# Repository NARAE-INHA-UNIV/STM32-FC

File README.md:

**본 문서는 STM32 firmware만을 다루고 있습니다.**

> [[STM32-FC-docs]](https://github.com/NARAE-INHA-UNIV/STM32-FC-docs) How to use, Specification <br>
> [[STM32-FC-hw]](https://github.com/NARAE-INHA-UNIV/STM32-FC-hw) KiCAD, Schematic, PCB Artwork <br>
> [[MiniLink_cli]](https://github.com/NARAE-INHA-UNIV/MiniLink_cli) Data analysis like msg, log, param <br>

-----

# STM32 FC

인하대학교 모형항공기 동아리 나래에서 2024년 동계 UAV 활동으로 진행한 프로젝트임. <br>
회로와 펌웨어를 개발하되, 기성 pixhawk 모듈과 호환성을 가지기 위해 pixhawk 6C mini의 인터페이스와 흡사하게 제작하는 것을 목표로함. <br>

- 활동명 : [UAV] FC 제작 활동
- 일시 : 2024 동계 방학 - 진행중
- 팀명 :  항공전자 (구 FC)
- 팀장 : 정영우(2025), 이현제(2024)

## 폴더 구조

`Plane` 폴더가 STM32Cube IDE 프로젝트이다. 주로 수정할 코드는 `Core` 디렉토리 내에 위치한다.

`Plane` -> `Core` -> `Src/Inc`

- Src : Source code (.c)
- Inc : header (.h)
  - {Module Name}.h
  - {Module Name}_module.h
  - {Module Name}_common.h
  - {Module Name}_type.h

{Module Name} 앞의 접두사의 의미 :
- `FC` : 보드 내부 HW 관리 (UART, RC, Servo etc.)
- `AP` : 고수준의 제어기나 자율 비행 (Failsafe, RTH etc.)
- `SEN` : 외부 센서

헤더 파일 중 `driver.h`는 외부 모듈에서 접근할 떄 사용한다. <br>
예를 들어 `main.c`가 `RadioContol` 모듈에 접근할 때 `FC_RC/driver.h`에 접근해야 한다. `RadioContol.h`는 해당 모듈 내부에서 사용하는 코드로 외부에서 직접 접근하지 않도록 한다.

```bash
├─AP_Failsafe       # Failsafe 관련 코드
├─FC_AHRS           # IMU 센서, 기압 센서
├─FC_Basic          # Buzzer나 LED 등
├─FC_RC             # 라디오 조종기 (스펙트럼, PPM, ELRS)
├─FC_Servo          # 서보 모터, ESC
├─FC_Serial         # Serial 기능
│  └─MiniLink       # 외부 장치와 통신하는 프로토콜
│      └─Param      # 파라미터 관리
└─test              # 테스트 중인 코드
```

## 기여 (개발)

1. 프로젝트 fork
2. fork된 개인 레파지토리 clone
3. 코드 작성
4. 개인 레파지토리에 커밋 & 푸시
5. Pull-request

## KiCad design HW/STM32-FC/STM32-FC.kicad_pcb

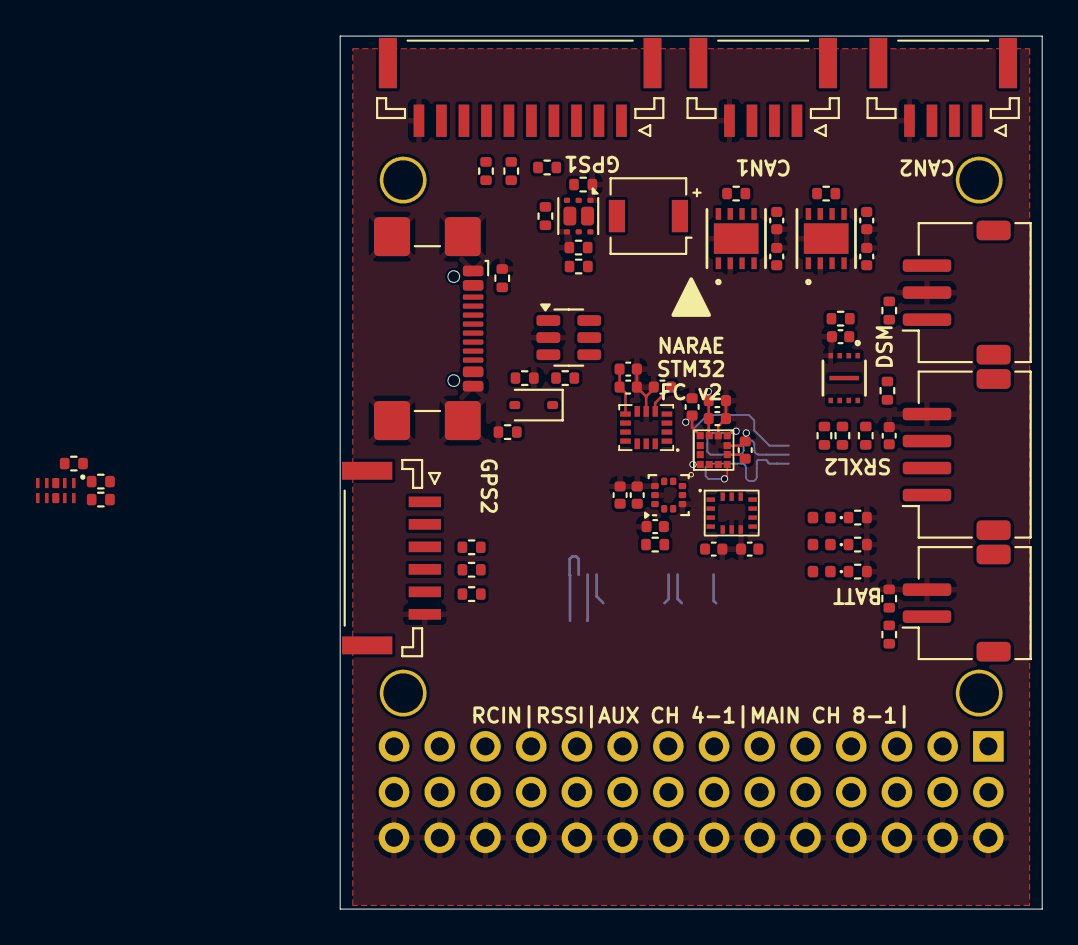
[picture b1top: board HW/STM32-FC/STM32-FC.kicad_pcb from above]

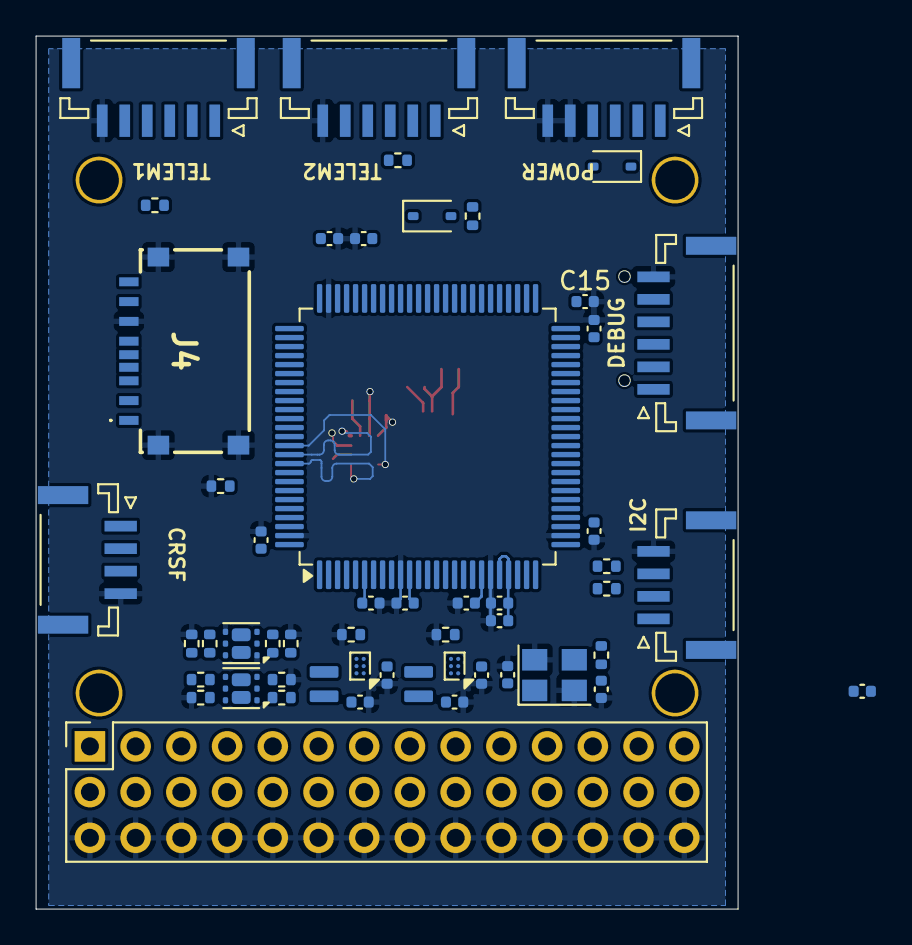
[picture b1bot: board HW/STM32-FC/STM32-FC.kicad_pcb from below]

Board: 4 copper layers, 39.0 x 48.5 mm, 129 parts (53 on the bottom side), 120 nets.

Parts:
BZ1: FUET-4020
C1, C4: 10pF; C_0402_1005Metric
C2, C14, C16, C27: 4.7uF; C_0402_1005Metric
C3, C5, C8, C9, C10, C11, C13, C15, C20, C21, C22, C23, C24, C29, C30, C32, C33, C34, C35, C36, C37: 100nF; C_0402_1005Metric
C6, C7, C25: 2.2uF; C_0402_1005Metric
C12: 1uF; C_0402_1005Metric
C17, C19, C28: 10uF; C_0402_1005Metric
C26: 10nF; C_0402_1005Metric
C31: 220nF; C_0402_1005Metric
D1, D5, D6: B5819W; D_SOD-323
D2: Red; LED_0402_1005Metric
D3: Yellow; LED_0402_1005Metric
D4: Green; LED_0402_1005Metric
H1, H2, H3, H4: MountingHole; MountingHole_2.2mm_M2
J1, J3, J11, J12, J13: GH 1.25mm 6P; JST_GH_SM06B-GHS-TB_06x1.25mm_Angled
J2: USB_C_USB2.0_14P; USB_C_Receptacle_GCT_USB4110
J4: TF-06A; TF06A
J5: JST ZH 1.5mm 2P; JST_ZH_S2B-ZR-SM4A-TF_1x02-1MP_P1.50mm_Horizontal
J6: PWM_Conn_3x14
J7: ZH 1.5mm 4P; JST_ZH_S4B-ZR-SM4A-TF_1x04-1MP_P1.50mm_Horizontal
J8, J14, J15, J16: GH 1.25mm 4P; JST_GH_SM04B-GHS-TB_04x1.25mm_Angled
J9: ZH 1.5mm 3P; JST_ZH_S3B-ZR-SM4A-TF_1x03-1MP_P1.50mm_Horizontal
J10: GH 1.25mm 10P; JST_GH_SM10B-GHS-TB_10x1.25mm_Angled
L1, L3: 2.2u; VLS201610ET-2R2M
Q1, Q2: PMDPB30XN; Nexperia_SOT1118
Q3: PMDPB55XP; Nexperia_SOT1118
R1, R2, R5, R11, R12, R23, R24, R25, R26, R27, R28, R31, R32, R34, R36, R37, R38, R39, R40, R41, R42, R43, R44, R45, R46, R47: 10k; R_0402_1005Metric
R3, R4, R6, R7, R8, R9, R10, R33, R48, R49: 120; R_0402_1005Metric
R13, R14: 5k1; R_0402_1005Metric
R15, R16, R17, R18, R30, R35: 1k; R_0402_1005Metric
R19: 1k5; R_0402_1005Metric
R20, R22: 267k; R_0402_1005Metric
R29: 15k; R_0402_1005Metric
U1: STM32F407VETx; LQFP-100_14x14mm_P0.5mm
U2: USBLC6-2SC6; SOT-23-6
U3, U5: TPS62840; Texas_DSBGA-6_0.855x1.255mm_Layout2x3_P0.4mm_LevelC
U6: W25X40CLUXIG; USON_LUXIG TR_WIN-L
U7: BMI323; BMI323_L
U8: ICM-42688-P; IIM42352_L
U9: LIS2MDLTR
U10: LPS22HH; ST_HLGA-10_2x2mm_P0.5mm_LayoutBorder3x2y
U11: TMUX1104
U12, U13: ATA6561-GBQW; VDFN8_3X3_MCH-L
Y1: 16MHz; Crystal_SMD_Abracon_ABM8G-4Pin_3.2x2.5mm

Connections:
+3.3V: C2.1, C3.1, C8.1, C9.1, C10.1, C11.1, C12.1, C13.1, C15.1, C17.1, C19.1, C20.1, C21.1, C22.1, C23.1, C24.2, C25.1, C26.1, C27.2, C28.1, C29.1, C30.1, C32.2, C33.2, C36.2, C37.2, J1.1, J4.4 (VDD), J9.1, J10.8, L1.2, L3.2, R19.1, R23.1, R24.1, R25.1, R26.1, R28.1, R35.1, R36.1, R38.1, R39.1, R40.1, R41.1, R42.1, R43.1, R44.1, R45.1, R46.1, R47.1, U1.6 (VBAT), U1.11 (VDD), U1.19 (VDD), U1.21 (VREF+), U1.22 (VDDA), U1.28 (VDD), U1.50 (VDD), U1.75 (VDD), U1.100 (VDD), U3.A2 (VOS), U5.A2 (VOS), U6.3 (~WP), U6.7 (~HOLD), U6.8 (VCC), U7.5 (VDDIO), U7.8 (VDD), U8.5 (VDDIO), U8.8 (VDD), U9.9 (VDD), U9.10 (VDD_IO), U10.1 (Vdd_IO), U10.10 (VDD), U11.5 (EN), U11.6 (VDD), U12.5 (VIO), U13.5 (VIO)
+5V: BZ1.1 (-), C14.1, C16.1, C34.2, C35.2, D1.1 (K), D5.1 (K), D6.1 (K), J6.17 (5V_RCIN), J6.18 (5V_RSSI), J7.3, J8.3, J10.1, J11.1, J12.1, J13.1, J14.1, J15.1, J16.1, Q3.1 (S), Q3.4 (S), R15.1, R16.1, U3.B1 (VIN), U3.C1 (EN), U5.B1 (VIN), U12.3 (VCC), U13.3 (VCC)
+5V_PWM1: J6.15 (5V_A), Q3.6 (D), Q3.7 (D), R17.1
+5V_PWM2: J6.16 (5V_B), Q3.3 (D), Q3.8 (D), R18.1
+BATT: J5.1, R29.1
/BARO_INT: U1.38 (PE7), U10.7 (INT_DRDY)
/BARO_NSS: R28.2, U1.5 (PE6), U10.6 (~CS)
/BOOT0: J1.5, R2.1, U1.94 (BOOT0)
/Buzzer: R4.1, U1.61 (PD14)
/CAN1_RX: U1.81 (PD0), U12.4 (RXD)
/CAN1_STBY: U1.33 (PC4), U12.8 (STBY)
/CAN1_TX: U1.82 (PD1), U12.1 (TXD)
/CAN2_RX: U1.51 (PB12), U13.4 (RXD)
/CAN2_STBY: U1.34 (PC5), U13.8 (STBY)
/CAN2_TX: U1.92 (PB6), U13.1 (TXD)
/Communication/CAN1_N: J15.3, R48.2, U12.6 (CANL)
/Communication/CAN1_P: J15.2, R48.1, U12.7 (CANH)
/Communication/CAN2_N: J16.3, R49.2, U13.6 (CANL)
/Communication/CAN2_P: J16.2, R49.1, U13.7 (CANH)
/FLASH_NSS: U1.7 (PC13), U6.1 (~CS)
/GPS1_BUZZER: J10.9, U1.65 (PC8)
/GPS1_SW: J10.6, U1.60 (PD13)
/GPS1_SW_LED: J10.7, U1.57 (PD10)
/GYRO1_INT: U1.39 (PE8), U8.4 (INT1/INT)
/GYRO1_NSS: U1.4 (PE5), U8.12 (AP_CS)
/GYRO2_INT: U1.8 (PC14), U7.4 (INT1)
/GYRO2_NSS: U1.2 (PE3), U7.12 (CSB)
/I2C1_SCL: J14.2, R47.2, U1.95 (PB8)
/I2C1_SDA: J14.3, R46.2, U1.96 (PB9)
/I2C2_SCL: J11.4, R42.2, U1.47 (PB10)
/I2C2_SDA: J11.5, R40.2, U1.48 (PB11)
/I2C3_SCL: J10.4, R39.2, U1.67 (PA8)
/I2C3_SDA: J10.5, R38.2, U1.66 (PC9)
/LED_GREEN: D4.2 (A), U1.1 (PE2)
/LED_RED: D2.2 (A), U1.97 (PE0)
/LED_YELLOW: D3.2 (A), U1.98 (PE1)
/MAG_NSS: U1.3 (PE4), U9.3 (CS)
/MSD_DETECT: R27.1, U1.9 (PC15)
/MSD_NSS: J4.2 (CS), R26.2, U1.88 (PD7)
/NRST: C5.1, J1.4, U1.14 (NRST)
/OSC_IN: C1.2, U1.12 (PH0), Y1.1
/OSC_OUT: R3.2, U1.13 (PH1)
/PM_CURRENT: J3.3, U1.17 (PC2)
/PM_VOLTAGE: J3.4, U1.18 (PC3)
/PWR_SEL0: R9.1, U1.46 (PE15)
/PWR_SEL1: R10.1, U1.77 (PA15)
/RC_INPUT/RCIN: J6.14 (RCIN), U11.8 (D)
/RC_INPUT/SBUS: R33.1, U11.9 (S2)
/RC_PPM: R37.1, U1.45 (PE14), U11.2 (S1)
/RC_RX: J8.2, J9.3, Q1.3 (D), Q1.8 (D), R35.2, R36.2, U1.69 (PA10), U11.4 (S3)
/RC_SEL0: R31.1, U1.41 (PE10), U11.1 (A0)
/RC_SEL1: R32.1, U1.40 (PE9), U11.10 (A1)
/RC_TX: J7.1, J8.1, U1.68 (PA9), U11.7 (S4)
/RSSI_IN: J6.13 (RSSI), U1.16 (PC1)
/SPI1_MISO: U1.31 (PA6), U8.1 (AP_SDO/AP_AD0), U10.5 (SA0)
/SPI1_MOSI: U1.32 (PA7), U8.14 (AP_SDA/AP_SDIO/AP_SDI), U10.4 (SDA)
/SPI1_SCK: U1.30 (PA5), U8.13 (AP_SCL/AP_SCLK), U10.2 (SCL)
/SPI2_MISO: J4.7 (DO), R23.2, U1.53 (PB14), U6.2 (DO(IO1))
/SPI2_MOSI: J4.3 (DI), R25.2, U1.54 (PB15), U6.5 (DI(IO0))
/SPI2_SCK: J4.5 (SCLK), R24.2, U1.52 (PB13), U6.6 (SCK)
/SPI3_MISO: U1.90 (PB4), U7.1 (SDO), U9.7 (INT/DRDY/SDO)
/SPI3_MOSI: U1.91 (PB5), U7.14 (SDX), U9.4 (SDA/SDI/SDO)
/SPI3_SCK: U1.89 (PB3), U7.13 (SCX), U9.1 (SCL/SPC)
/SWCLK: J1.3, U1.76 (PA14)
/SWDIO: J1.2, U1.72 (PA13)
/SW_PWR_IMU: U1.43 (PE12), U5.C1 (EN)
/TIM1_CH2: J6.11 (CH11), U1.42 (PE11)
/TIM1_CH3: J6.12 (CH12), U1.44 (PE13)
/TIM3_CH1: J6.2 (CH2), U1.63 (PC6)
/TIM3_CH2: J6.3 (CH3), U1.64 (PC7)
/TIM3_CH3: J6.9 (CH9), U1.35 (PB0)
/TIM3_CH4: J6.10 (CH10), U1.36 (PB1)
/TIM4_CH2: J6.1 (CH1), U1.93 (PB7)
/TIM4_CH4: J6.4 (CH4), U1.62 (PD15)
/TIM5_CH1: J6.5 (CH5), U1.23 (PA0)
/TIM5_CH2: J6.6 (CH6), U1.24 (PA1)
/TIM5_CH3: J6.7 (CH7), U1.25 (PA2)
/TIM5_CH4: J6.8 (CH8), U1.26 (PA3)
/UART2_CTS: J12.4, U1.84 (PD3)
/UART2_RTS: J12.5, U1.85 (PD4)
/UART2_RX: J12.3, R44.2, U1.87 (PD6)
/UART2_TX: J12.2, U1.86 (PD5)
/UART3_CTS: J13.4, U1.58 (PD11)
/UART3_RTS: J13.5, U1.59 (PD12)
/UART3_RX: J13.3, R45.2, U1.56 (PD9)
/UART3_TX: J13.2, U1.55 (PD8)
/UART4_RX: J10.3, R41.2, U1.79 (PC11)
/UART4_TX: J10.2, U1.78 (PC10)
/UART5_RX: J11.3, R43.2, U1.83 (PD2)
/UART5_TX: J11.2, U1.80 (PC12)
/USB & POWER/USB_CONN_D+: J2.A6 (D+), J2.B6 (D+), U2.3 (I/O2)
/USB & POWER/USB_CONN_D-: J2.A7 (D-), J2.B7 (D-), U2.1 (I/O1)
/USB_D+: R19.2, U1.71 (PA12), U2.4 (I/O2)
/USB_D-: U1.70 (PA11), U2.6 (I/O1)
/VCAP1: C6.2, U1.49 (VCAP_1)
/VCAP2: C7.1, U1.73 (VCAP_2)
/V_BATT: R29.2, R30.1, U1.15 (PC0)
GND: C1.1, C2.2, C3.2, C4.2, C5.2, C6.1, C7.2, C8.2, C9.2, C10.2, C11.2, C12.2, C13.2, C14.2, C15.2, C16.2, C17.2, C19.2, C20.2, C21.2, C22.2, C23.2, C24.1, C25.2, C26.2, C27.1, C28.2, C29.2, C30.2, C31.2, C32.1, C33.1, C34.1, C35.1, C36.1, C37.1, J1.6, J2.A1 (GND), J2.A12 (GND), J2.B1 (GND), J2.B12 (GND), J2.S1 (SHIELD), J3.5, J3.6, J4.6 (VSS), J4.MP1, J4.MP2, J4.MP3, J4.MP4, J5.2, J6.19 (GND), J7.4, J8.4, J9.2, J10.10, J11.6, J12.6, J13.6, J14.4, J15.4, J16.4, Q1.1 (S), Q1.4 (S), Q2.1 (S), Q2.4 (S), R1.2, R2.2, R5.2, R6.2, R7.2, R8.2, R11.2, R12.2, R13.2, R14.2, R17.2, R18.2, R20.1, R22.1, R30.2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
unnamed: BZ1.2 (+), D1.2 (A), Q1.6 (D), Q1.7 (D)
unnamed: C4.1, R3.1, Y1.3
unnamed: D2.1 (K), R6.1
unnamed: D3.1 (K), R7.1
unnamed: D4.1 (K), R8.1
unnamed: D6.2 (A), J3.1, J3.2
unnamed: J2.A5 (CC1), R13.1
unnamed: J2.B5 (CC2), R14.1
unnamed: J4.G1 (SWICTH), R27.2
unnamed: Q1.2 (G), R4.2, R5.1
unnamed: Q1.5 (G), R33.2, R34.1
unnamed: Q2.2 (G), R9.2, R11.1
unnamed: Q2.5 (G), R10.2, R12.1
unnamed: Q2.6 (D), Q2.7 (D), Q3.2 (G), R15.2
unnamed: Q2.3 (D), Q2.8 (D), Q3.5 (G), R16.2
unnamed: R1.1, U1.37 (PB2)
unnamed: L1.1, U3.B2 (SW)
unnamed: R20.2, U3.C2 (VSET)
unnamed: L3.1, U5.B2 (SW)
unnamed: R22.2, U5.C2 (VSET)
unnamed: C31.1, U9.5 (C1)
VBUS: D5.2 (A), J2.A4 (VBUS), J2.A9 (VBUS), J2.B4 (VBUS), J2.B9 (VBUS), U2.5 (VBUS)

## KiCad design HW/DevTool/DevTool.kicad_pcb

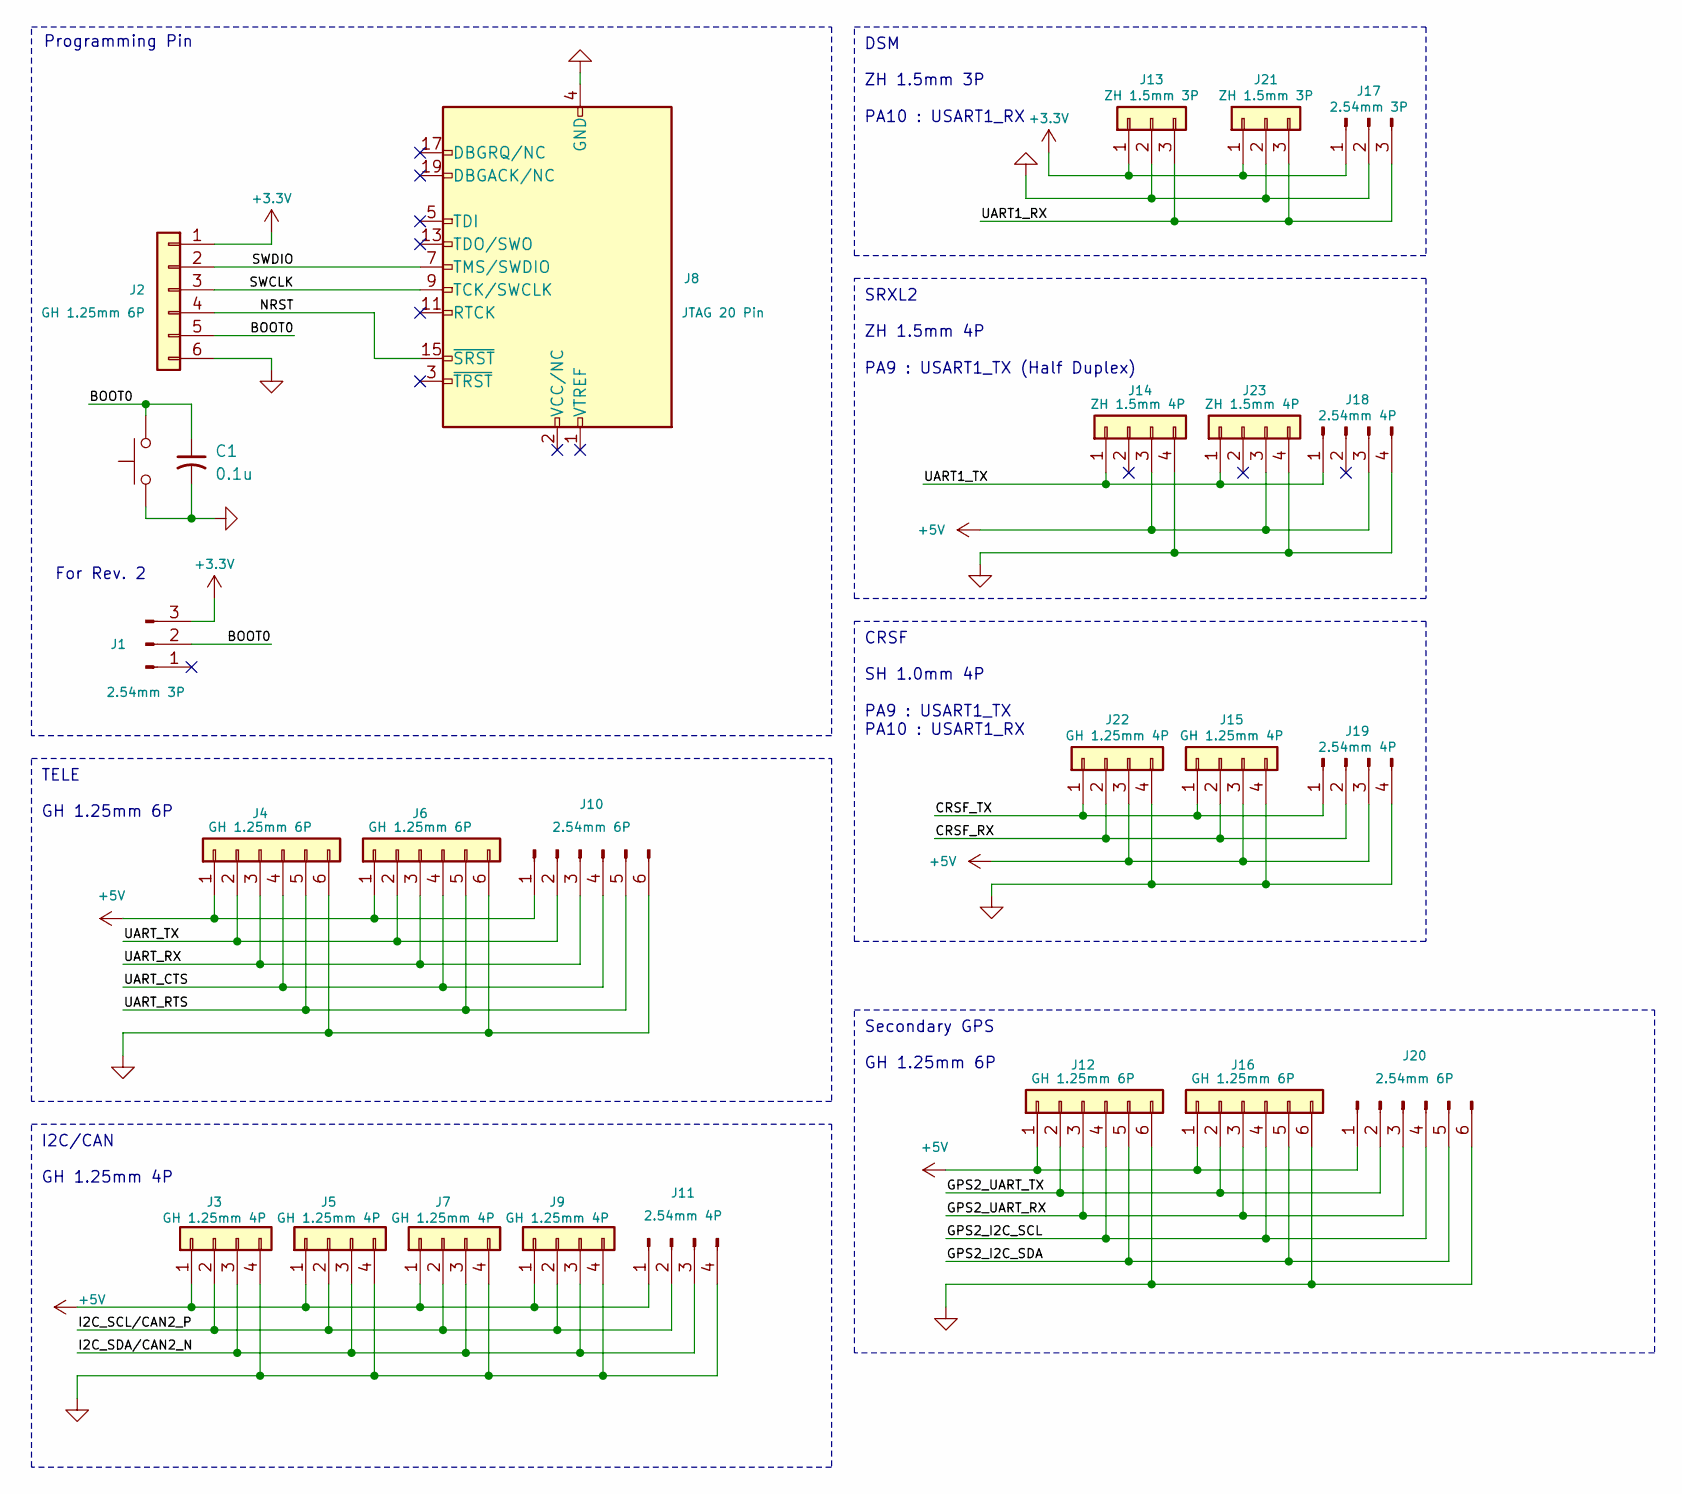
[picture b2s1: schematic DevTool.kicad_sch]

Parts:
C1: 0.1u; C_0603_1608Metric
J1, J17: 2.54mm 3P; PinHeader_1x03_P2.54mm_Vertical
J2, J4, J6, J12, J16: GH 1.25mm 6P; JST_GH_BM06B-GHS-TBT_06; LCSC C133065
J3, J5, J7, J9, J15, J22: GH 1.25mm 4P; JST_GH_BM04B-GHS-TBT_04; LCSC C189895
J8: JTAG 20 Pin; IDC-Header_2x10_P2.54mm_Vertical
J10, J20: 2.54mm 6P; PinHeader_1x06_P2.54mm_Vertical
J11, J18, J19: 2.54mm 4P; PinHeader_1x04_P2.54mm_Vertical
J13, J21: ZH 1.5mm 3P; JST_ZH_S3B-ZR-SM4A-TF_1x03-1MP_P1.50mm_Horizontal; LCSC C72591
J14, J23: ZH 1.5mm 4P; JST_ZH_S4B-ZR-SM4A-TF_1x04-1MP_P1.50mm_Horizontal; LCSC C485354
SW1: SW_Push; SW_SPST_PTS645

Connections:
+3.3V: J1.3, J2.1, J13.1, J17.1, J21.1
+5V: J3.1, J4.1, J5.1, J6.1, J7.1, J9.1, J10.1, J11.1, J12.1, J14.3, J15.3, J16.1, J18.3, J19.3, J20.1, J22.3, J23.3
/BOOT0: C1.1, J1.2, J2.5, SW1.2
/CRSF_RX: J15.2, J19.2, J22.2
/CRSF_TX: J15.1, J19.1, J22.1
/GPS2_I2C_SCL: J12.4, J16.4, J20.4
/GPS2_I2C_SDA: J12.5, J16.5, J20.5
/GPS2_UART_RX: J12.3, J16.3, J20.3
/GPS2_UART_TX: J12.2, J16.2, J20.2
/I2C_SCL/CAN2_P: J3.2, J5.2, J7.2, J9.2, J11.2
/I2C_SDA/CAN2_N: J3.3, J5.3, J7.3, J9.3, J11.3
/NRST: J2.4, J8.15 (~SRST)
/SWCLK: J2.3, J8.9 (TCK/SWCLK)
/SWDIO: J2.2, J8.7 (TMS/SWDIO)
/UART1_RX: J13.3, J17.3, J21.3
/UART1_TX: J14.1, J18.1, J23.1
/UART_CTS: J4.4, J6.4, J10.4
/UART_RTS: J4.5, J6.5, J10.5
/UART_RX: J4.3, J6.3, J10.3
/UART_TX: J4.2, J6.2, J10.2
GND: C1.2, J2.6, J3.4, J4.6, J5.4, J6.6, J7.4, J8.4 (GND), J8.6 (GND), J8.8 (GND), J8.10 (GND), J8.12 (GND), J8.14 (GND), J8.16 (GND), J8.18 (GND), J8.20 (GND), J9.4, J10.6, J11.4, J12.6, J13.2, J14.4, J15.4, J16.6, J17.2, J18.4, J19.4, J20.6, J21.2, J22.4, J23.4, SW1.1

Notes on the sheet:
SRXL2
CRSF
DSM
SH 1.0mm 4P PA9 : USART1_TX PA10 : USART1_RX
For Rev. 2
GH 1.25mm 6P
Programming Pin
TELE
GH 1.25mm 4P
ZH 1.5mm 3P PA10 : USART1_RX
I2C/CAN
Secondary GPS
ZH 1.5mm 4P PA9 : USART1_TX (Half Duplex)

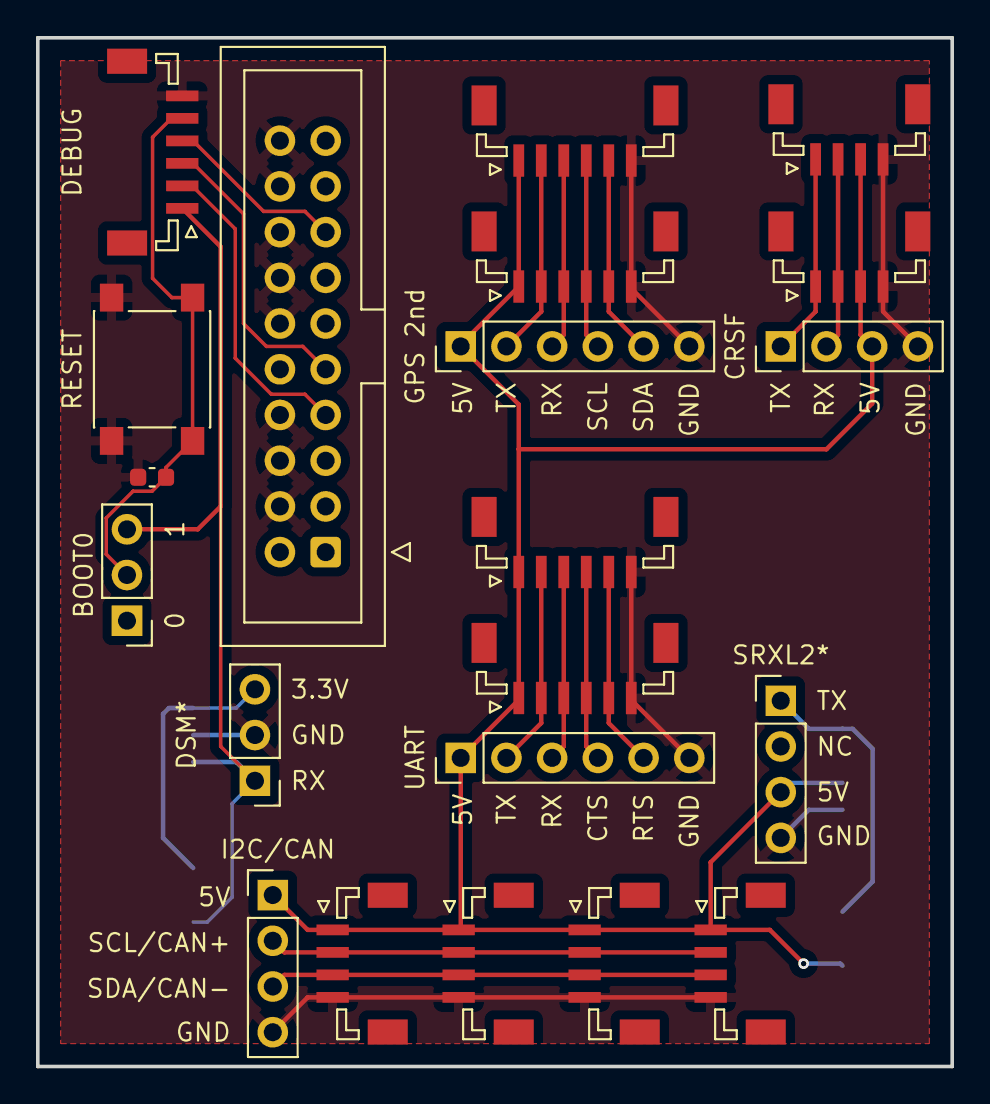
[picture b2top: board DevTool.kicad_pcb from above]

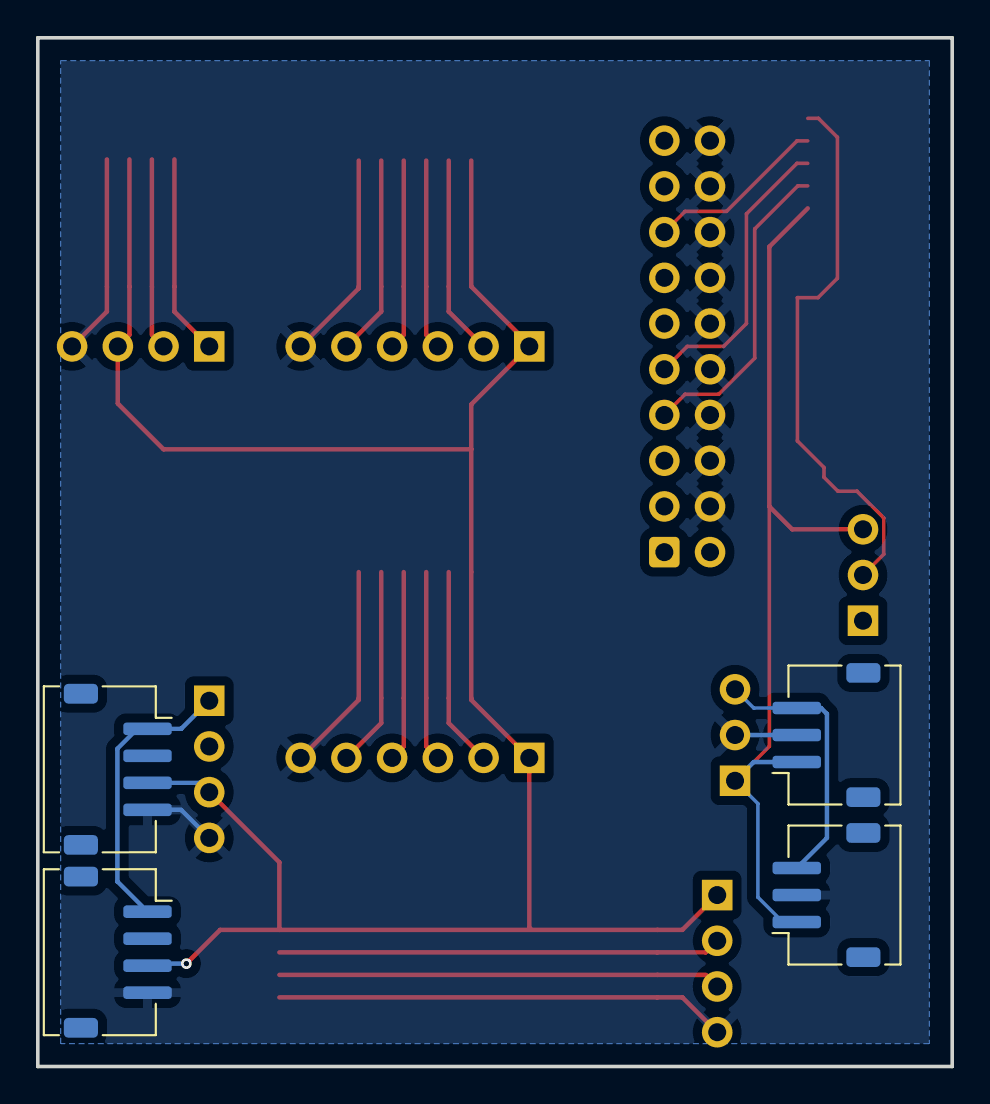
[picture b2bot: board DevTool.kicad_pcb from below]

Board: 2 copper layers, 50.8 x 57.2 mm, 25 parts (4 on the bottom side), 21 nets.

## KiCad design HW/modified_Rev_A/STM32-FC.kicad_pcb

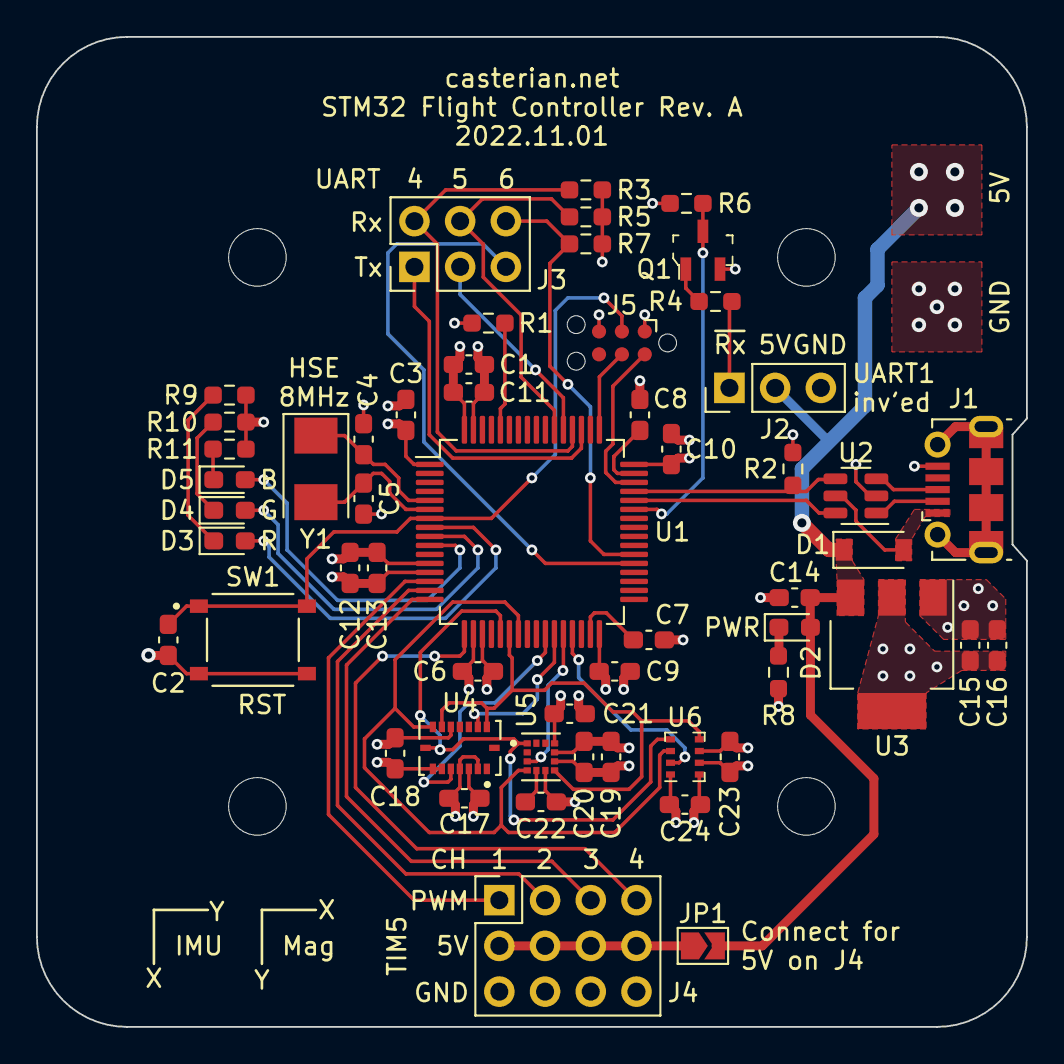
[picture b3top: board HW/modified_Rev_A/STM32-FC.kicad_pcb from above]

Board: 4 copper layers, 55.0 x 55.0 mm, 59 parts (0 on the bottom side), 45 nets.

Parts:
C1, C14, C16, C19: 10uF; C_0603_1608Metric_Pad1.08x0.95mm_HandSolder
C2, C3, C6, C9, C10, C11, C13, C15, C17, C18, C20, C21, C23, C24: 100nF; C_0603_1608Metric_Pad1.08x0.95mm_HandSolder
C4, C5: 30pF; C_0603_1608Metric_Pad1.08x0.95mm_HandSolder
C7, C8: 2.2uF; C_0603_1608Metric_Pad1.08x0.95mm_HandSolder
C12: 1uF; C_0603_1608Metric_Pad1.08x0.95mm_HandSolder
C22: 220nF; C_0603_1608Metric_Pad1.08x0.95mm_HandSolder
D1: B5819W; D_SOD-123
D2, D3: Red; LED_0603_1608Metric_Pad1.05x0.95mm_HandSolder
D4: Green; LED_0603_1608Metric_Pad1.05x0.95mm_HandSolder
D5: Blue; LED_0603_1608Metric_Pad1.05x0.95mm_HandSolder
H1, H2, H3, H4: MountingHole; MountingHole_3.2mm_M3
J1: USB_B_Micro; USB_Micro-B_Molex-105017-0001
J2: 2.54mm Male; PinHeader_1x03_P2.54mm_Vertical
J3: 2.54mm Male; PinHeader_2x03_P2.54mm_Vertical
J4: PWM_Conn_3x04
J5: TC2030-IDC; Tag-Connect_TC2030-IDC-NL_2x03_P1.27mm_Vertical
JP1: Jumper; SolderJumper-2_P1.3mm_Open_TrianglePad1.0x1.5mm
Q1: S9013; SOT-23-3
R1: 100k; R_0603_1608Metric_Pad0.98x0.95mm_HandSolder
R2: 1.5k; R_0603_1608Metric_Pad0.98x0.95mm_HandSolder
R3, R5, R6, R7: 10k; R_0603_1608Metric_Pad0.98x0.95mm_HandSolder
R4, R8, R9, R10, R11: 1k; R_0603_1608Metric_Pad0.98x0.95mm_HandSolder
SW1: Tactile Switch; SW_TS-1187A-B-A-B
U1: STM32F405RGTx; LQFP-64_10x10mm_P0.5mm
U2: USBLC6-2SC6; SOT-23-6
U3: AMS1117-3.3; SOT-223-3_TabPin2
U4: BMI088; PQFN50P450X300X100-16N
U5: LIS2MDLTR; PQFN50P200X200X70-12N
U6: BMP280; Bosch_LGA-8_2x2.5mm_P0.65mm_ClockwisePinNumbering
Y1: 8MHz; Crystal_SMD_5032-2Pin_5.0x3.2mm

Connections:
+3.3V: C1.1, C3.1, C6.1, C9.1, C10.1, C11.1, C12.1, C13.1, C15.1, C16.1, C17.1, C18.1, C19.1, C20.1, C21.1, C23.1, C24.1, J5.1, R2.1, R3.1, R5.1, R6.1, R7.1, U1.1 (VBAT), U1.13 (VDDA), U1.19 (VDD), U1.32 (VDD), U1.48 (VDD), U1.64 (VDD), U3.2 (VO), U4.3 (VDD), U4.11 (VDDIO), U5.9 (VDD), U5.10 (VDD_IO), U6.6 (VDDIO), U6.8 (VDD)
+5V: C14.1, D1.1 (K), D2.2 (A), J2.2, JP1.2 (B), U3.3 (VI)
/ACC_NSS: U1.27 (PB1), U4.14 (CSB1)
/BARO_NSS: U1.29 (PB10), U6.2 (CSB)
/BOOT0: R1.1, U1.60 (BOOT0)
/GYRO_NSS: U1.26 (PB0), U4.5 (CSB2)
/LED_BLUE: D5.2 (A), U1.10 (PC2)
/LED_GREEN: D4.2 (A), U1.9 (PC1)
/LED_RED: D3.2 (A), U1.8 (PC0)
/MAG_NSS: U1.28 (PB2), U5.3 (CS)
/NRST: C2.2, J5.3, SW1.1 (A), U1.7 (NRST)
/OSC_IN: C4.2, U1.5 (PH0), Y1.1
/OSC_OUT: C5.1, U1.6 (PH1), Y1.2
/PWM_5V: J4.5 (5V), JP1.1 (A)
/SPI1_MISO: U1.22 (PA6), U4.10 (SDO2), U4.15 (SDO1), U5.7 (INT/DRDY/SDO), U6.5 (SDO)
/SPI1_MOSI: U1.23 (PA7), U4.9 (SDA/SDI), U5.4 (SDA/SDI/SDO), U6.3 (SDI)
/SPI1_SCK: U1.21 (PA5), U4.8 (SCL/SCK), U5.1 (SCL/SPC), U6.4 (SCK)
/SWCLK: J5.4, U1.49 (PA14)
/SWDIO: J5.2, U1.46 (PA13)
/Sensors/MAG_C1: C22.1, U5.5 (C1)
/TIM5_CH1: J4.1 (CH1), U1.14 (PA0)
/TIM5_CH2: J4.2 (CH2), U1.15 (PA1)
/TIM5_CH3: J4.3 (CH3), U1.16 (PA2)
/TIM5_CH4: J4.4 (CH4), U1.17 (PA3)
/UART1_RX: Q1.3 (C), R6.2, U1.43 (PA10)
/UART1_RX_INV: J2.1, R4.1
/UART4_RX: J3.2, R3.2, U1.52 (PC11)
/UART4_TX: J3.1, U1.51 (PC10)
/UART5_RX: J3.4, R5.2, U1.54 (PD2)
/UART5_TX: J3.3, U1.53 (PC12)
/UART6_RX: J3.6, R7.2, U1.38 (PC7)
/UART6_TX: J3.5, U1.37 (PC6)
/USB_CONN_D+: J1.3 (D+), U2.3 (I/O2)
/USB_CONN_D-: J1.2 (D-), U2.1 (I/O1)
/USB_D+: R2.2, U1.45 (PA12), U2.4 (I/O2)
/USB_D-: U1.44 (PA11), U2.6 (I/O1)
/VCAP1: C7.2, U1.31 (VCAP_1)
/VCAP2: C8.1, U1.47 (VCAP_2)
GND: C1.2, C2.1, C3.2, C4.1, C5.2, C6.2, C7.1, C8.2, C9.2, C10.2, C11.2, C12.2, C13.2, C14.2, C15.2, C16.2, C17.2, C18.2, C19.2, C20.2, C21.2, C22.2, C23.2, C24.2, J1.5 (GND), J2.3, J4.6 (GND), J5.5, Q1.2 (E), R1.2, R8.2, R9.2, R10.2, R11.2, SW1.2 (B), U1.12 (VSSA), U1.18 (VSS), U1.63 (VSS), U2.2 (GND), U3.1 (GND), U4.2 (NC), U4.4 (GNDA), U4.6 (GNDIO), U4.7 (PS), U5.6 (GND), U5.8 (GND), U6.1 (GND), U6.7 (GND)
unnamed: D2.1 (K), R8.1
unnamed: D3.1 (K), R9.1
unnamed: D4.1 (K), R10.1
unnamed: D5.1 (K), R11.1
unnamed: Q1.1 (B), R4.2
VBUS: D1.2 (A), J1.1 (VBUS), U2.5 (VBUS)

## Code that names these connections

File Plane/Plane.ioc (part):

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Mcu.Name=STM32F407V(E-G)Tx
Mcu.Package=LQFP100
Mcu.UserName=STM32F407VETx
PA0-WKUP.GPIOParameters=GPIO_Label
PA0-WKUP.GPIO_Label=MAIN_CH5
PA0-WKUP.Signal=S_TIM5_CH1
PA1.GPIOParameters=GPIO_Label
PA1.GPIO_Label=MAIN_CH6
PA1.Signal=S_TIM5_CH2
PA11.Mode=Device_Only
PA11.Signal=USB_OTG_FS_DM
PA12.Mode=Device_Only
PA12.Signal=USB_OTG_FS_DP
PA13.Mode=Serial_Wire
PA13.Signal=SYS_JTMS-SWDIO
PA14.Mode=Serial_Wire
PA14.Signal=SYS_JTCK-SWCLK
PA2.GPIOParameters=GPIO_Label
PA2.GPIO_Label=MAIN_CH7
PA2.Signal=S_TIM5_CH3
PA3.GPIOParameters=GPIO_Label
PA3.GPIO_Label=MAIN_CH8
PA3.Signal=S_TIM5_CH4
PA5.GPIOParameters=GPIO_PuPd,GPIO_Mode
PA5.GPIO_Mode=GPIO_MODE_AF_PP
PA5.GPIO_PuPd=GPIO_NOPULL
PA5.Mode=Full_Duplex_Master
PA5.Signal=SPI1_SCK
PA6.Mode=Full_Duplex_Master
PA6.Signal=SPI1_MISO
PA7.Mode=Full_Duplex_Master
PA7.Signal=SPI1_MOSI
PA8.GPIOParameters=GPIO_Label
PA8.GPIO_Label=GPS1_SCL
PA8.Mode=I2C
PA8.Signal=I2C3_SCL
PA9.GPIOParameters=GPIO_PuPd,GPIO_Label,GPIO_ModeDefaultOD
PA9.GPIO_Label=RC_SRXL2
PA9.GPIO_ModeDefaultOD=GPIO_MODE_AF_PP
PA9.GPIO_PuPd=GPIO_PULLUP
PA9.Mode=Half_duplex(single_wire_mode)
PA9.Signal=USART1_TX
PB0.GPIOParameters=GPIO_Label
PB0.GPIO_Label=MAIN_CH9
PB0.Signal=S_TIM3_CH3
PB1.GPIOParameters=GPIO_Label
PB1.GPIO_Label=MAIN_CH10
PB1.Signal=S_TIM3_CH4
PB10.GPIOParameters=GPIO_Label
PB10.GPIO_Label=GPS2_SCL
PB10.Mode=I2C
PB10.Signal=I2C2_SCL
PB11.GPIOParameters=GPIO_Label
PB11.GPIO_Label=GPS2_SCL
PB11.Mode=I2C
PB11.Signal=I2C2_SDA
PB12.Mode=CAN_Activate
PB12.Signal=CAN2_RX
PB13.Mode=Full_Duplex_Master
PB13.Signal=SPI2_SCK
PB14.Mode=Full_Duplex_Master
PB14.Signal=SPI2_MISO
PB15.Mode=Full_Duplex_Master
PB15.Signal=SPI2_MOSI
PB3.GPIOParameters=GPIO_PuPd
PB3.GPIO_PuPd=GPIO_NOPULL
PB3.Mode=Full_Duplex_Master
PB3.Signal=SPI3_SCK
PB4.GPIOParameters=GPIO_PuPd
PB4.GPIO_PuPd=GPIO_NOPULL
PB4.Mode=Full_Duplex_Master
PB4.Signal=SPI3_MISO
PB5.GPIOParameters=GPIO_PuPd
PB5.GPIO_PuPd=GPIO_NOPULL
PB5.Mode=Full_Duplex_Master
PB5.Signal=SPI3_MOSI
PB6.Mode=CAN_Activate
PB6.Signal=CAN2_TX
PB7.GPIOParameters=GPIO_Label
PB7.GPIO_Label=MAIN_CH1
PB7.Signal=S_TIM4_CH2
PB8.Mode=I2C
PB8.Signal=I2C1_SCL
PB9.Mode=I2C
PB9.Signal=I2C1_SDA
PC0.GPIOParameters=GPIO_Label
PC0.GPIO_Label=V_BATT
PC0.Signal=ADCx_IN10
PC1.GPIOParameters=GPIO_Label
PC1.GPIO_Label=RSSI
PC1.Signal=ADCx_IN11
PC10.GPIOParameters=GPIO_Label
PC10.GPIO_Label=GPS1_TX
PC10.Mode=Asynchronous
PC10.Signal=UART4_TX
PC11.GPIOParameters=GPIO_Label
PC11.GPIO_Label=GPS1_RX
PC11.Mode=Asynchronous
PC11.Signal=UART4_RX
PC12.GPIOParameters=GPIO_Label
PC12.GPIO_Label=GPS2_TX
PC12.Mode=Asynchronous
PC12.Signal=UART5_TX
PC13-ANTI_TAMP.GPIOParameters=GPIO_Label
PC13-ANTI_TAMP.GPIO_Label=FLASH_NSS
PC13-ANTI_TAMP.Signal=GPIO_Output
PC15-OSC32_OUT.GPIOParameters=GPIO_Label
PC15-OSC32_OUT.GPIO_Label=MSD_DETECT
PC15-OSC32_OUT.Signal=GPIO_Input
PC2.GPIOParameters=GPIO_Label
PC2.GPIO_Label=PM_CURRENT
PC2.Signal=ADCx_IN12
PC3.GPIOParameters=GPIO_Label
PC3.GPIO_Label=PM_VOLTAGE
PC3.Signal=ADCx_IN13
PC4.GPIOParameters=GPIO_Label
PC4.GPIO_Label=CAN1_STBY
PC4.Signal=GPIO_Output
PC5.GPIOParameters=GPIO_Label
PC5.GPIO_Label=CAN2_STBY
PC5.Signal=GPIO_Output
PC6.GPIOParameters=GPIO_Label
PC6.GPIO_Label=MAIN_CH2
PC6.Signal=S_TIM3_CH1
PC7.GPIOParameters=GPIO_Label
PC7.GPIO_Label=MAIN_CH3
PC7.Signal=S_TIM3_CH2
PC9.GPIOParameters=GPIO_Label
PC9.GPIO_Label=GPS1_SDA
PC9.Mode=I2C
PC9.Signal=I2C3_SDA
PD0.Mode=CAN_Activate
PD0.Signal=CAN1_RX
PD1.Mode=CAN_Activate
PD1.Signal=CAN1_TX
PD10.GPIOParameters=GPIO_Label
PD10.GPIO_Label=GPS1_SW_LED 
PD10.Signal=GPIO_Output
PD11.Signal=USART3_CTS
PD12.Signal=USART3_RTS
PD13.GPIOParameters=GPIO_Label
PD13.GPIO_Label=GPS1_SW
PD13.Signal=GPIO_Input
PD14.GPIOParameters=GPIO_Label
PD14.GPIO_Label=Buzzer
PD14.Signal=S_TIM4_CH3
PD15.GPIOParameters=GPIO_Label
PD15.GPIO_Label=MAIN_CH4
PD15.Signal=S_TIM4_CH4
PD2.GPIOParameters=GPIO_Label
PD2.GPIO_Label=GPS2_RX
PD2.Mode=Asynchronous
PD2.Signal=UART5_RX
PD3.Signal=USART2_CTS
PD4.Signal=USART2_RTS
PD5.GPIOParameters=GPIO_Label
PD5.GPIO_Label=Telm1_TX
PD5.Mode=Asynchronous
PD5.Signal=USART2_TX
PD6.GPIOParameters=GPIO_Label
PD6.GPIO_Label=Telm1_RX
PD6.Mode=Asynchronous
PD6.Signal=USART2_RX
PD8.GPIOParameters=GPIO_Label
PD8.GPIO_Label=Telm2_TX
PD8.Mode=Asynchronous
PD8.Signal=USART3_TX
PD9.GPIOParameters=GPIO_Label
PD9.GPIO_Label=Telm2_RX
PD9.Mode=Asynchronous
PD9.Signal=USART3_RX
PE0.GPIOParameters=GPIO_Label
PE0.GPIO_Label=LED_RED
PE0.Signal=GPIO_Output
PE1.GPIOParameters=GPIO_Label
PE1.GPIO_Label=LED_YELLOW
PE1.Signal=GPIO_Output
PE11.GPIOParameters=GPIO_Label
PE11.GPIO_Label=MAIN_CH11
PE11.Signal=S_TIM1_CH2
PE13.GPIOParameters=GPIO_Label
PE13.GPIO_Label=MAIN_CH12
PE13.Signal=S_TIM1_CH3
PE14.GPIOParameters=GPIO_Label,GPIO_ModeDefaultEXTI
PE14.GPIO_Label=PPM_IN
PE14.GPIO_ModeDefaultEXTI=GPIO_MODE_IT_FALLING
PE14.Signal=GPXTI14
PE2.GPIOParameters=GPIO_Label
PE2.GPIO_Label=LED_BLUE
PE2.Signal=GPIO_Output
PE3.GPIOParameters=GPIO_PuPd,GPIO_Label
PE3.GPIO_Label=GYRO2_NSS
PE3.GPIO_PuPd=GPIO_NOPULL
PE3.Signal=GPIO_Output
PE4.GPIOParameters=GPIO_Label
PE4.GPIO_Label=MAG_NSS
PE4.Signal=GPIO_Output
PE5.GPIOParameters=GPIO_PuPd,GPIO_Label
PE5.GPIO_Label=GYRO1_NSS
PE5.GPIO_PuPd=GPIO_NOPULL
PE5.Signal=GPIO_Output
PE6.GPIOParameters=GPIO_PuPd,GPIO_Label
PE6.GPIO_Label=BARO_NSS
PE6.GPIO_PuPd=GPIO_NOPULL
PE6.Signal=GPIO_Output
PE7.GPIOParameters=GPIO_Label
PE7.GPIO_Label=BARO_INT
PE7.Signal=GPIO_Input
PH0-OSC_IN.Mode=HSE-External-Oscillator
PH0-OSC_IN.Signal=RCC_OSC_IN
PH1-OSC_OUT.Mode=HSE-External-Oscillator
PH1-OSC_OUT.Signal=RCC_OSC_OUT
RCC.HSE_VALUE=16000000
RCC.SYSCLKFreq_VALUE=168000000
RCC.SYSCLKSource=RCC_SYSCLKSOURCE_PLLCLK
board=custom

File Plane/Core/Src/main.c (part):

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
  LL_AHB1_GRP1_EnableClock(LL_AHB1_GRP1_PERIPH_GPIOC);
  /**ADC1 GPIO Configuration
  PC0   ------> ADC1_IN10
  PC1   ------> ADC1_IN11
  PC2   ------> ADC1_IN12
  PC3   ------> ADC1_IN13
  */
  GPIO_InitStruct.Pin = V_BATT_Pin|RSSI_Pin|PM_CURRENT_Pin|PM_VOLTAGE_Pin;
  GPIO_InitStruct.Mode = LL_GPIO_MODE_ANALOG;
  GPIO_InitStruct.Pull = LL_GPIO_PULL_NO;
  LL_GPIO_Init(GPIOC, &GPIO_InitStruct);
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
  LL_AHB1_GRP1_EnableClock(LL_AHB1_GRP1_PERIPH_GPIOB);
  /**I2C1 GPIO Configuration
  PB8   ------> I2C1_SCL
  PB9   ------> I2C1_SDA
  */
  GPIO_InitStruct.Pin = LL_GPIO_PIN_8|LL_GPIO_PIN_9;
  GPIO_InitStruct.Mode = LL_GPIO_MODE_ALTERNATE;
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
  LL_AHB1_GRP1_EnableClock(LL_AHB1_GRP1_PERIPH_GPIOB);
  /**I2C2 GPIO Configuration
  PB10   ------> I2C2_SCL
  PB11   ------> I2C2_SDA
  */
  GPIO_InitStruct.Pin = GPS2_SCL_Pin|GPS2_SCLB11_Pin;
  GPIO_InitStruct.Mode = LL_GPIO_MODE_ALTERNATE;
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  LL_AHB1_GRP1_EnableClock(LL_AHB1_GRP1_PERIPH_GPIOC);
  LL_AHB1_GRP1_EnableClock(LL_AHB1_GRP1_PERIPH_GPIOA);
  /**I2C3 GPIO Configuration
  PC9   ------> I2C3_SDA
  PA8   ------> I2C3_SCL
  */
  GPIO_InitStruct.Pin = GPS1_SDA_Pin;
  GPIO_InitStruct.Mode = LL_GPIO_MODE_ALTERNATE;
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
  LL_AHB1_GRP1_EnableClock(LL_AHB1_GRP1_PERIPH_GPIOA);
  /**SPI1 GPIO Configuration
  PA5   ------> SPI1_SCK
  PA6   ------> SPI1_MISO
  PA7   ------> SPI1_MOSI
  */
  GPIO_InitStruct.Pin = LL_GPIO_PIN_5|LL_GPIO_PIN_6|LL_GPIO_PIN_7;
  GPIO_InitStruct.Mode = LL_GPIO_MODE_ALTERNATE;
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
  LL_AHB1_GRP1_EnableClock(LL_AHB1_GRP1_PERIPH_GPIOB);
  /**SPI2 GPIO Configuration
  PB13   ------> SPI2_SCK
  PB14   ------> SPI2_MISO
  PB15   ------> SPI2_MOSI
  */
  GPIO_InitStruct.Pin = LL_GPIO_PIN_13|LL_GPIO_PIN_14|LL_GPIO_PIN_15;
  GPIO_InitStruct.Mode = LL_GPIO_MODE_ALTERNATE;
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
  LL_AHB1_GRP1_EnableClock(LL_AHB1_GRP1_PERIPH_GPIOB);
  /**SPI3 GPIO Configuration
  PB3   ------> SPI3_SCK
  PB4   ------> SPI3_MISO
  PB5   ------> SPI3_MOSI
  */
  GPIO_InitStruct.Pin = LL_GPIO_PIN_3|LL_GPIO_PIN_4|LL_GPIO_PIN_5;
  GPIO_InitStruct.Mode = LL_GPIO_MODE_ALTERNATE;
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  /* USER CODE END TIM1_Init 2 */
  LL_AHB1_GRP1_EnableClock(LL_AHB1_GRP1_PERIPH_GPIOE);
  /**TIM1 GPIO Configuration
  PE11   ------> TIM1_CH2
  PE13   ------> TIM1_CH3
  */
  GPIO_InitStruct.Pin = MAIN_CH11_Pin|MAIN_CH12_Pin;
  GPIO_InitStruct.Mode = LL_GPIO_MODE_ALTERNATE;
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  LL_AHB1_GRP1_EnableClock(LL_AHB1_GRP1_PERIPH_GPIOB);
  LL_AHB1_GRP1_EnableClock(LL_AHB1_GRP1_PERIPH_GPIOC);
  /**TIM3 GPIO Configuration
  PB0   ------> TIM3_CH3
  PB1   ------> TIM3_CH4
  PC6   ------> TIM3_CH1
  PC7   ------> TIM3_CH2
  */
  GPIO_InitStruct.Pin = MAIN_CH9_Pin|MAIN_CH10_Pin;
  GPIO_InitStruct.Mode = LL_GPIO_MODE_ALTERNATE;
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  LL_AHB1_GRP1_EnableClock(LL_AHB1_GRP1_PERIPH_GPIOD);
  LL_AHB1_GRP1_EnableClock(LL_AHB1_GRP1_PERIPH_GPIOB);
  /**TIM4 GPIO Configuration
  PD14   ------> TIM4_CH3
  PD15   ------> TIM4_CH4
  PB7   ------> TIM4_CH2
  */
  GPIO_InitStruct.Pin = Buzzer_Pin|MAIN_CH4_Pin;
  GPIO_InitStruct.Mode = LL_GPIO_MODE_ALTERNATE;
  GPIO_InitStruct.Speed = LL_GPIO_SPEED_FREQ_LOW;
  GPIO_InitStruct.OutputType = LL_GPIO_OUTPUT_PUSHPULL;
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  /* USER CODE END TIM5_Init 2 */
  LL_AHB1_GRP1_EnableClock(LL_AHB1_GRP1_PERIPH_GPIOA);
  /**TIM5 GPIO Configuration
  PA0-WKUP   ------> TIM5_CH1
  PA1   ------> TIM5_CH2
  PA2   ------> TIM5_CH3
  PA3   ------> TIM5_CH4
  */
  GPIO_InitStruct.Pin = MAIN_CH5_Pin|MAIN_CH6_Pin|MAIN_CH7_Pin|MAIN_CH8_Pin;
  GPIO_InitStruct.Mode = LL_GPIO_MODE_ALTERNATE;
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
  LL_AHB1_GRP1_EnableClock(LL_AHB1_GRP1_PERIPH_GPIOC);
  /**UART4 GPIO Configuration
  PC10   ------> UART4_TX
  PC11   ------> UART4_RX
  */
  GPIO_InitStruct.Pin = GPS1_TX_Pin|GPS1_RX_Pin;
  GPIO_InitStruct.Mode = LL_GPIO_MODE_ALTERNATE;
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  LL_AHB1_GRP1_EnableClock(LL_AHB1_GRP1_PERIPH_GPIOC);
  LL_AHB1_GRP1_EnableClock(LL_AHB1_GRP1_PERIPH_GPIOD);
  /**UART5 GPIO Configuration
  PC12   ------> UART5_TX
  PD2   ------> UART5_RX
  */
  GPIO_InitStruct.Pin = GPS2_TX_Pin;
  GPIO_InitStruct.Mode = LL_GPIO_MODE_ALTERNATE;
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
  LL_AHB1_GRP1_EnableClock(LL_AHB1_GRP1_PERIPH_GPIOA);
  /**USART1 GPIO Configuration
  PA9   ------> USART1_TX
  */
  GPIO_InitStruct.Pin = RC_SRXL2_Pin;
  GPIO_InitStruct.Mode = LL_GPIO_MODE_ALTERNATE;
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
  LL_AHB1_GRP1_EnableClock(LL_AHB1_GRP1_PERIPH_GPIOD);
  /**USART2 GPIO Configuration
  PD3   ------> USART2_CTS
  PD4   ------> USART2_RTS
  PD5   ------> USART2_TX
  PD6   ------> USART2_RX
  */
  GPIO_InitStruct.Pin = LL_GPIO_PIN_3|LL_GPIO_PIN_4|Telm1_TX_Pin|Telm1_RX_Pin;
  GPIO_InitStruct.Mode = LL_GPIO_MODE_ALTERNATE;
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
  LL_AHB1_GRP1_EnableClock(LL_AHB1_GRP1_PERIPH_GPIOD);
  /**USART3 GPIO Configuration
  PD8   ------> USART3_TX
  PD9   ------> USART3_RX
  PD11   ------> USART3_CTS
  PD12   ------> USART3_RTS
  */
  GPIO_InitStruct.Pin = Telm2_TX_Pin|Telm2_RX_Pin|LL_GPIO_PIN_11|LL_GPIO_PIN_12;
  GPIO_InitStruct.Mode = LL_GPIO_MODE_ALTERNATE;
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  LL_AHB1_GRP1_EnableClock(LL_AHB1_GRP1_PERIPH_GPIOD);

  /**/
  LL_GPIO_ResetOutputPin(GPIOE, LED_BLUE_Pin|GYRO2_NSS_Pin|MAG_NSS_Pin|GYRO1_NSS_Pin
                          |BARO_NSS_Pin|LED_RED_Pin|LED_YELLOW_Pin);

  /**/
  LL_GPIO_ResetOutputPin(GPIOC, FLASH_NSS_Pin|CAN1_STBY_Pin|CAN2_STBY_Pin);

  /**/
  LL_GPIO_ResetOutputPin(GPS1_SW_LED_GPIO_Port, GPS1_SW_LED_Pin);

  /**/
  GPIO_InitStruct.Pin = LED_BLUE_Pin|GYRO2_NSS_Pin|MAG_NSS_Pin|GYRO1_NSS_Pin
                          |BARO_NSS_Pin|LED_RED_Pin|LED_YELLOW_Pin;
  GPIO_InitStruct.Mode = LL_GPIO_MODE_OUTPUT;
  GPIO_InitStruct.Speed = LL_GPIO_SPEED_FREQ_LOW;
  GPIO_InitStruct.OutputType = LL_GPIO_OUTPUT_PUSHPULL;
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  LL_GPIO_Init(GPIOE, &GPIO_InitStruct);

  /**/
  GPIO_InitStruct.Pin = FLASH_NSS_Pin|CAN1_STBY_Pin|CAN2_STBY_Pin;
  GPIO_InitStruct.Mode = LL_GPIO_MODE_OUTPUT;
  GPIO_InitStruct.Speed = LL_GPIO_SPEED_FREQ_LOW;
  GPIO_InitStruct.OutputType = LL_GPIO_OUTPUT_PUSHPULL;
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  LL_GPIO_Init(GPIOC, &GPIO_InitStruct);

  /**/
  GPIO_InitStruct.Pin = MSD_DETECT_Pin;
  GPIO_InitStruct.Mode = LL_GPIO_MODE_INPUT;
  GPIO_InitStruct.Pull = LL_GPIO_PULL_NO;
  LL_GPIO_Init(MSD_DETECT_GPIO_Port, &GPIO_InitStruct);

  /**/
  GPIO_InitStruct.Pin = BARO_INT_Pin;
  GPIO_InitStruct.Mode = LL_GPIO_MODE_INPUT;
  GPIO_InitStruct.Pull = LL_GPIO_PULL_NO;
  LL_GPIO_Init(BARO_INT_GPIO_Port, &GPIO_InitStruct);

  /**/
  GPIO_InitStruct.Pin = GPS1_SW_LED_Pin;
  GPIO_InitStruct.Mode = LL_GPIO_MODE_OUTPUT;
  GPIO_InitStruct.Speed = LL_GPIO_SPEED_FREQ_LOW;
  GPIO_InitStruct.OutputType = LL_GPIO_OUTPUT_PUSHPULL;
  GPIO_InitStruct.Pull = LL_GPIO_PULL_NO;
  LL_GPIO_Init(GPS1_SW_LED_GPIO_Port, &GPIO_InitStruct);

  /**/
  GPIO_InitStruct.Pin = GPS1_SW_Pin;
  GPIO_InitStruct.Mode = LL_GPIO_MODE_INPUT;
  GPIO_InitStruct.Pull = LL_GPIO_PULL_NO;
  LL_GPIO_Init(GPS1_SW_GPIO_Port, &GPIO_InitStruct);

  /**/
  LL_SYSCFG_SetEXTISource(LL_SYSCFG_EXTI_PORTE, LL_SYSCFG_EXTI_LINE14);
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

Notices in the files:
Plane/Core/Src/main.c:
Copyright (c) 2025 STMicroelectronics.
All rights reserved.
This software is licensed under terms that can be found in the LICENSE file
